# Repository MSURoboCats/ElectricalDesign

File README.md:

# Robocats Club PCB Files Repository

## Overview
Welcome to the Robocats Club PCB Files Repository! This repository contains all the necessary PCB design files, schematics, and related documentation for our club's various electronics projects. Our aim is to create, share, and improve PCB designs that can be used in robotics, automation, and other related fields.

## Getting Started
To use these files, clone the repository to your local machine:

```bash
git clone https://github.com/MSURoboCats/PcbDesign.git
```

You will need KiCad 7.0 to open and edit the `.kicad_pcb` and schematic files.

## Contribution Guidelines
We welcome contributions from all club members and the broader community. To contribute:

1. **Fork the Repository**: Create your own fork of the project.
2. **Create a Feature Branch**: Make your changes in a new branch.
3. **Commit Your Changes**: Commit your changes with clear and detailed commit messages.
4. **Submit a Pull Request**: Create a pull request for your changes to be reviewed.

Please ensure your designs meet our design standards and include necessary documentation and comments.

## Project Status
- [NewSub2023]: In-progress
- [OldSub2022]: Completed

## License
This project is licensed under the [MIT License](LICENSE) - see the LICENSE file for details.

## Contact
- Lead Designer: Peter Buckley
- Email: peterbuckley3636@gmail.com

For more information or to get involved, please join our discord.

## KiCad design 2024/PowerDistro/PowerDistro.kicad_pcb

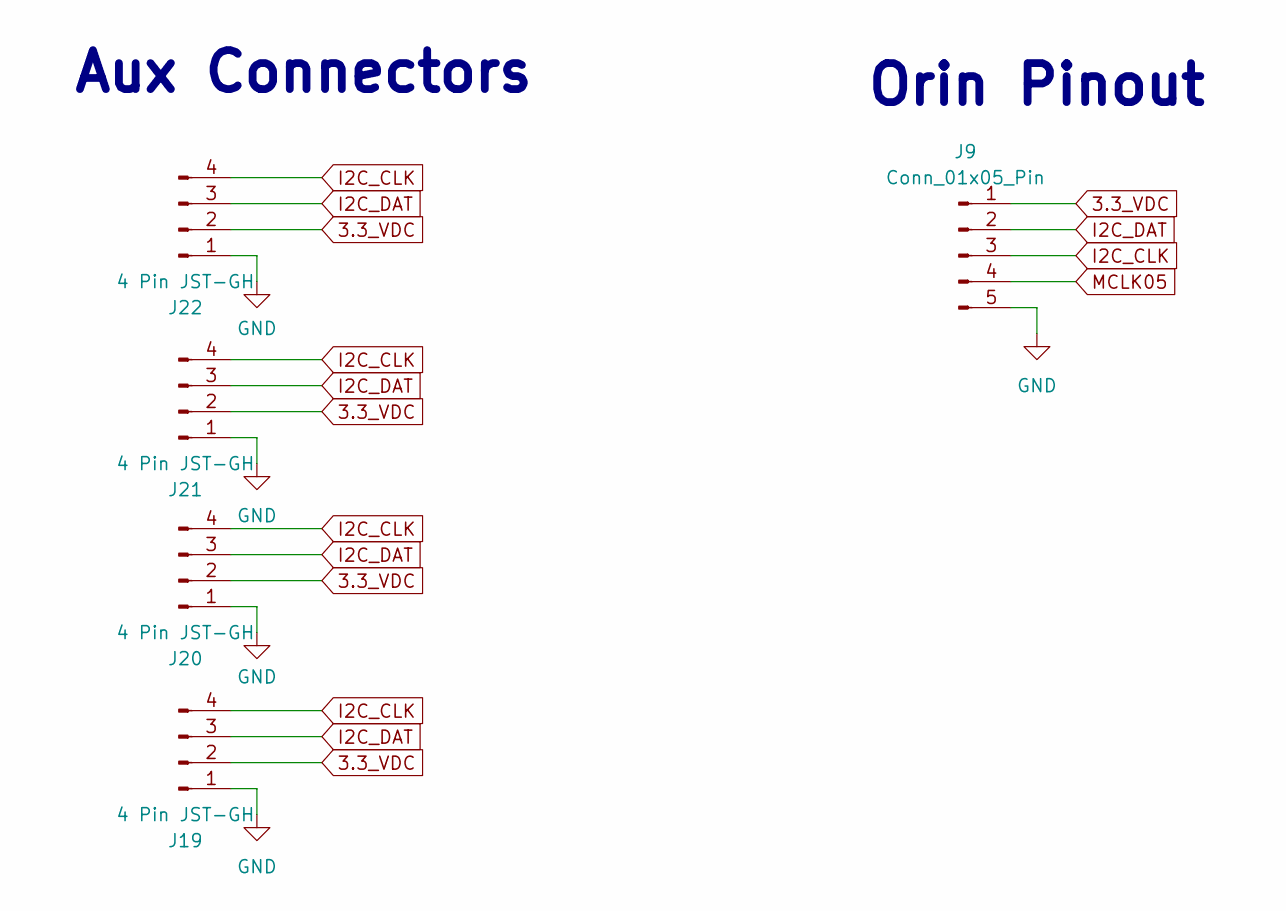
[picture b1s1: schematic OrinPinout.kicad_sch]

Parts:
J9: Conn_01x05_Pin; PinHeader_1x05_P2.54mm_Vertical
J19, J20, J21, J22: 4 Pin JST-GH; JST_XH_B4B-XH-A_1x04_P2.50mm_Vertical

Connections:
3.3_VDC: J9.1, J19.2, J20.2, J21.2, J22.2; also elsewhere on the board
GND: J9.5, J19.1, J20.1, J21.1, J22.1; also elsewhere on the board
I2C_CLK: J9.3, J19.4, J20.4, J21.4, J22.4; also elsewhere on the board
I2C_DAT: J9.2, J19.3, J20.3, J21.3, J22.3; also elsewhere on the board
MCLK05: J9.4

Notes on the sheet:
Orin Pinout
Aux Connectors

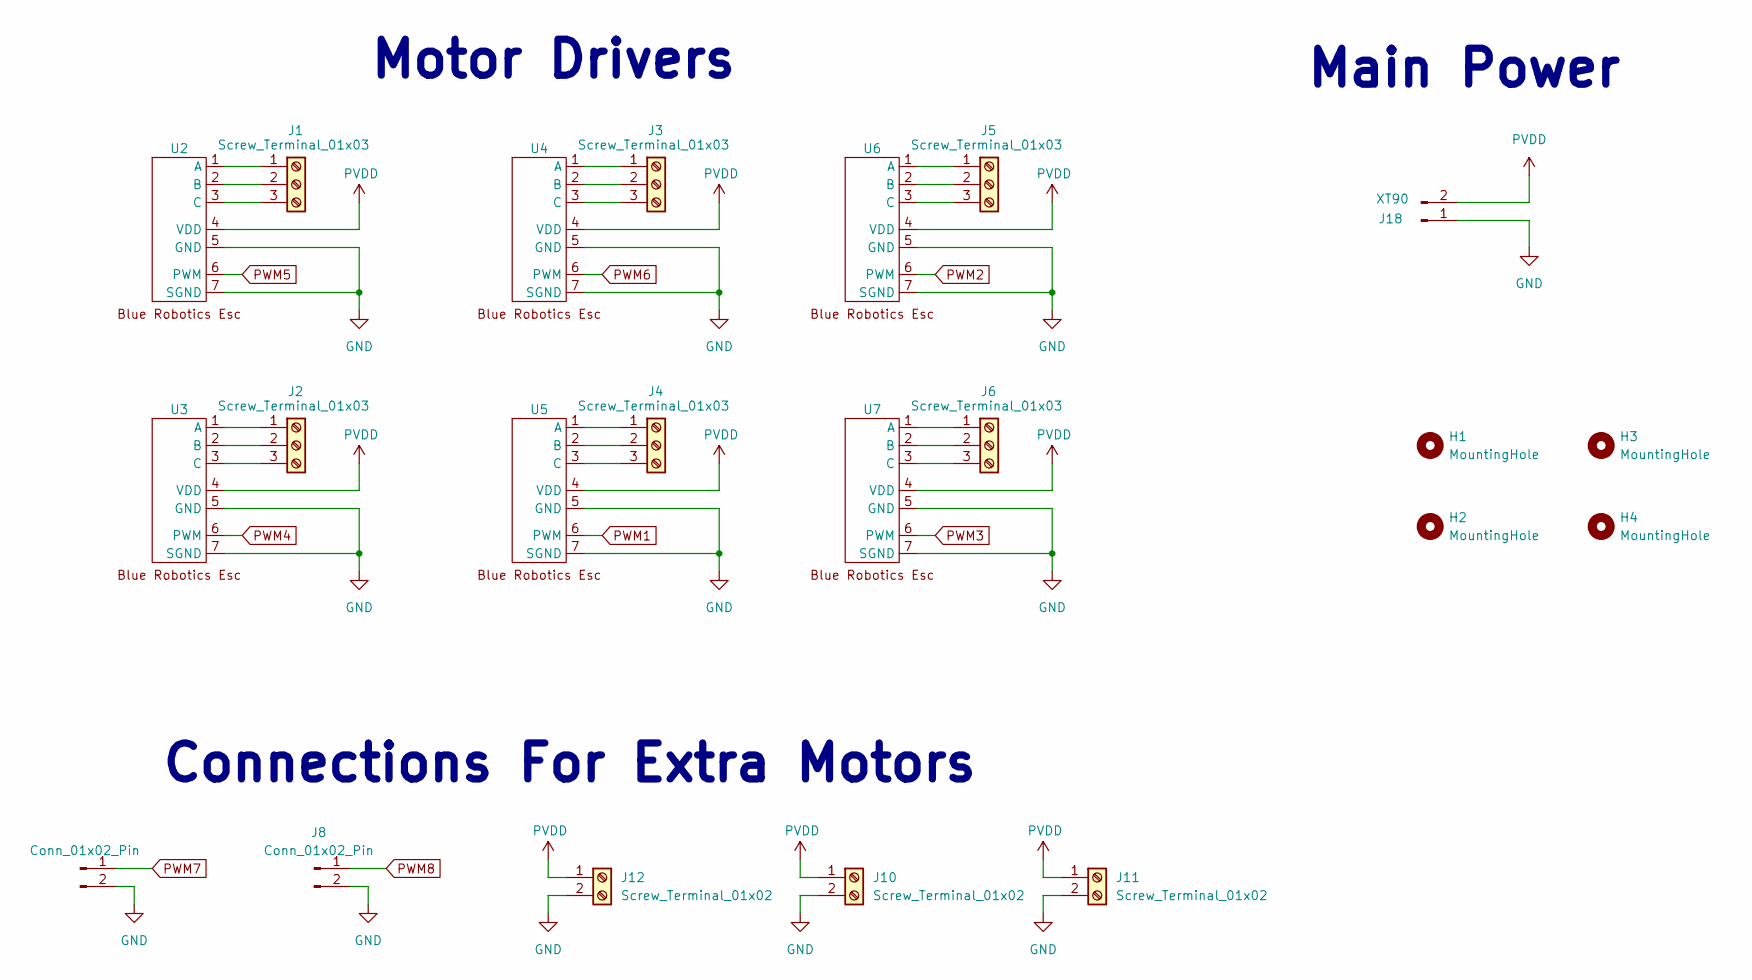
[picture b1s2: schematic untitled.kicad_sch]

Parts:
H1, H2, H3, H4: MountingHole; MountingHole_5.3mm_M5
J1, J2, J3, J4, J5, J6: Screw_Terminal_01x03; 691311500103
J7, J8: Conn_01x02_Pin; PinHeader_1x02_P2.54mm_Vertical
J10, J11, J12: Screw_Terminal_01x02; 691321100002
J18: XT90; XT90PB
U2, U3, U4, U5, U6, U7: BlueRoboticsESC

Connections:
GND: J7.2, J8.2, J10.2, J11.2, J12.2, J18.1, U2.5 (GND), U2.7 (SGND), U3.5 (GND), U3.7 (SGND), U4.5 (GND), U4.7 (SGND), U5.5 (GND), U5.7 (SGND), U6.5 (GND), U6.7 (SGND), U7.5 (GND), U7.7 (SGND); also elsewhere on the board
unnamed: J1.1, U2.1 (A)
unnamed: J1.2, U2.2 (B)
unnamed: J1.3, U2.3 (C)
unnamed: J2.1, U3.1 (A)
unnamed: J2.2, U3.2 (B)
unnamed: J2.3, U3.3 (C)
unnamed: J3.1, U4.1 (A)
unnamed: J3.2, U4.2 (B)
unnamed: J3.3, U4.3 (C)
unnamed: J4.1, U5.1 (A)
unnamed: J4.2, U5.2 (B)
unnamed: J4.3, U5.3 (C)
unnamed: J5.1, U6.1 (A)
unnamed: J5.2, U6.2 (B)
unnamed: J5.3, U6.3 (C)
unnamed: J6.1, U7.1 (A)
unnamed: J6.2, U7.2 (B)
unnamed: J6.3, U7.3 (C)
PVDD: J10.1, J11.1, J12.1, J18.2, U2.4 (VDD), U3.4 (VDD), U4.4 (VDD), U5.4 (VDD), U6.4 (VDD), U7.4 (VDD); also elsewhere on the board
PWM1: U5.6 (PWM); also elsewhere on the board
PWM2: U6.6 (PWM); also elsewhere on the board
PWM3: U7.6 (PWM); also elsewhere on the board
PWM4: U3.6 (PWM); also elsewhere on the board
PWM5: U2.6 (PWM); also elsewhere on the board
PWM6: U4.6 (PWM); also elsewhere on the board
PWM7: J7.1; also elsewhere on the board
PWM8: J8.1; also elsewhere on the board

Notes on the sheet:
Motor Drivers
Main Power
Connections For Extra Motors

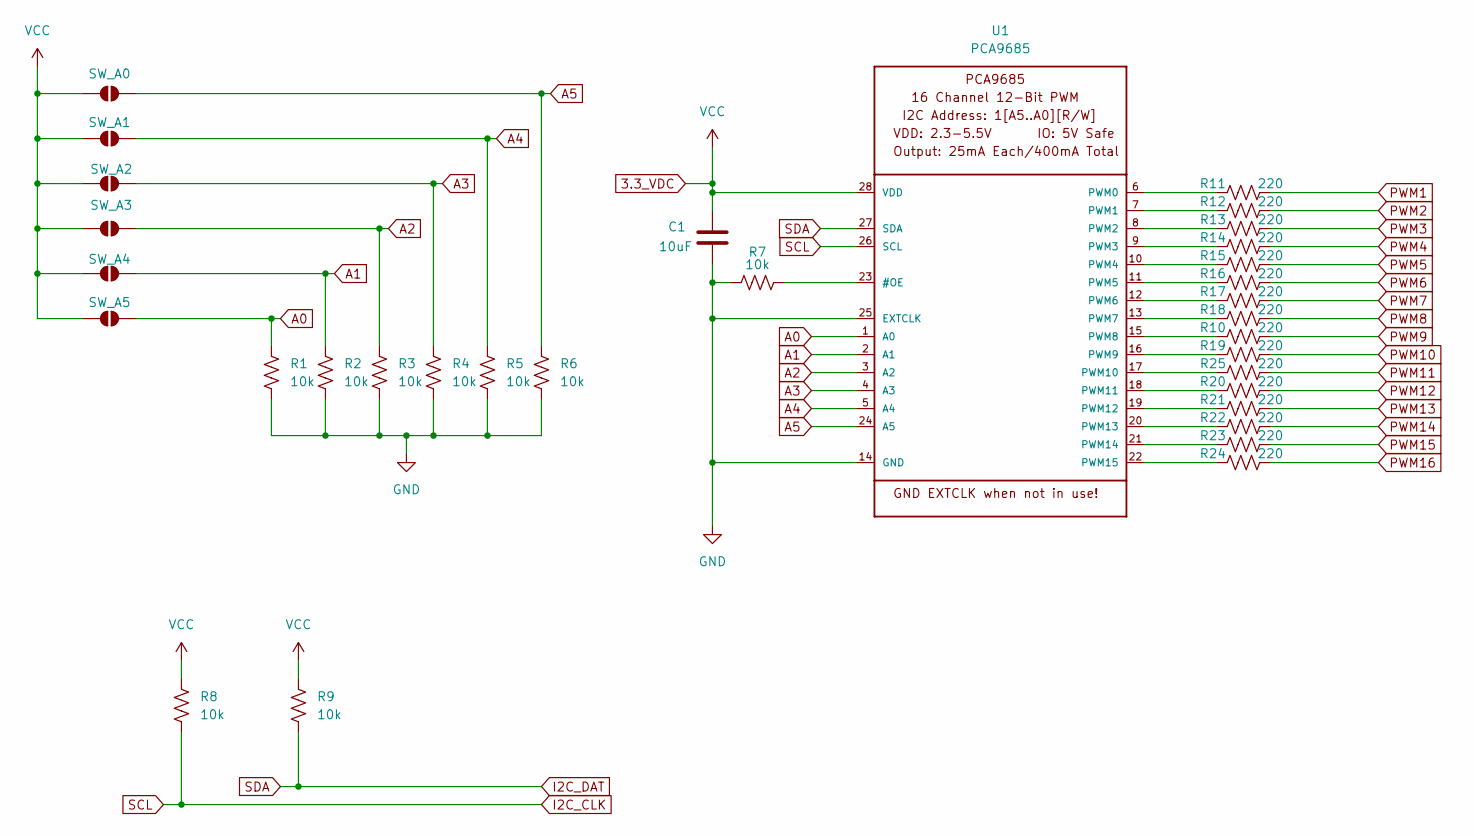
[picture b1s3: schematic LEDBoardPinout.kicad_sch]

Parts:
C1: 10uF; C_1206_3216Metric
R1, R2, R3, R4, R5, R6, R7, R8, R9: 10k; R_0603_1608Metric
R10, R11, R12, R13, R14, R15, R16, R17, R18, R19, R20, R21, R22, R23, R24, R25: 220; R_0603_1608Metric
SW_A0, SW_A1, SW_A2, SW_A3, SW_A4, SW_A5: SolderJumper_2_Open; SolderJumper-2_P1.3mm_Open_RoundedPad1.0x1.5mm
U1: PCA9685; TSSOP28

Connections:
3.3_VDC: C1.1, R8.1, R9.1, SW_A0.1 (A), SW_A1.1 (A), SW_A2.1 (A), SW_A3.1 (A), SW_A4.1 (A), SW_A5.1 (A), U1.28 (VDD); also elsewhere on the board
A0: R1.1, SW_A5.2 (B), U1.1 (A0)
A1: R2.1, SW_A4.2 (B), U1.2 (A1)
A2: R3.1, SW_A3.2 (B), U1.3 (A2)
A3: R4.1, SW_A2.2 (B), U1.4 (A3)
A4: R5.1, SW_A1.2 (B), U1.5 (A4)
A5: R6.1, SW_A0.2 (B), U1.24 (A5)
GND: C1.2, R1.2, R2.2, R3.2, R4.2, R5.2, R6.2, R7.2, U1.14 (GND), U1.25 (EXTCLK); also elsewhere on the board
I2C_CLK: R8.2, U1.26 (SCL); also elsewhere on the board
I2C_DAT: R9.2, U1.27 (SDA); also elsewhere on the board
unnamed: R7.1, U1.23 (#OE)
unnamed: R11.1, U1.6 (PWM0)
unnamed: R12.1, U1.7 (PWM1)
unnamed: R13.1, U1.8 (PWM2)
unnamed: R14.1, U1.9 (PWM3)
unnamed: R15.1, U1.10 (PWM4)
unnamed: R16.1, U1.11 (PWM5)
unnamed: R17.1, U1.12 (PWM6)
unnamed: R18.1, U1.13 (PWM7)
unnamed: R10.1, U1.15 (PWM8)
unnamed: R19.1, U1.16 (PWM9)
unnamed: R25.1, U1.17 (PWM10)
unnamed: R20.1, U1.18 (PWM11)
unnamed: R21.1, U1.19 (PWM12)
unnamed: R22.1, U1.20 (PWM13)
unnamed: R23.1, U1.21 (PWM14)
unnamed: R24.1, U1.22 (PWM15)
PWM1: R11.2; also elsewhere on the board
PWM2: R12.2; also elsewhere on the board
PWM3: R13.2; also elsewhere on the board
PWM4: R14.2; also elsewhere on the board
PWM5: R15.2; also elsewhere on the board
PWM6: R16.2; also elsewhere on the board
PWM7: R17.2; also elsewhere on the board
PWM8: R18.2; also elsewhere on the board
PWM9: R10.2; also elsewhere on the board
PWM10: R19.2; also elsewhere on the board
PWM11: R25.2; also elsewhere on the board
PWM12: R20.2; also elsewhere on the board
PWM13: R21.2; also elsewhere on the board
PWM14: R22.2; also elsewhere on the board
PWM15: R23.2; also elsewhere on the board
PWM16: R24.2; also elsewhere on the board

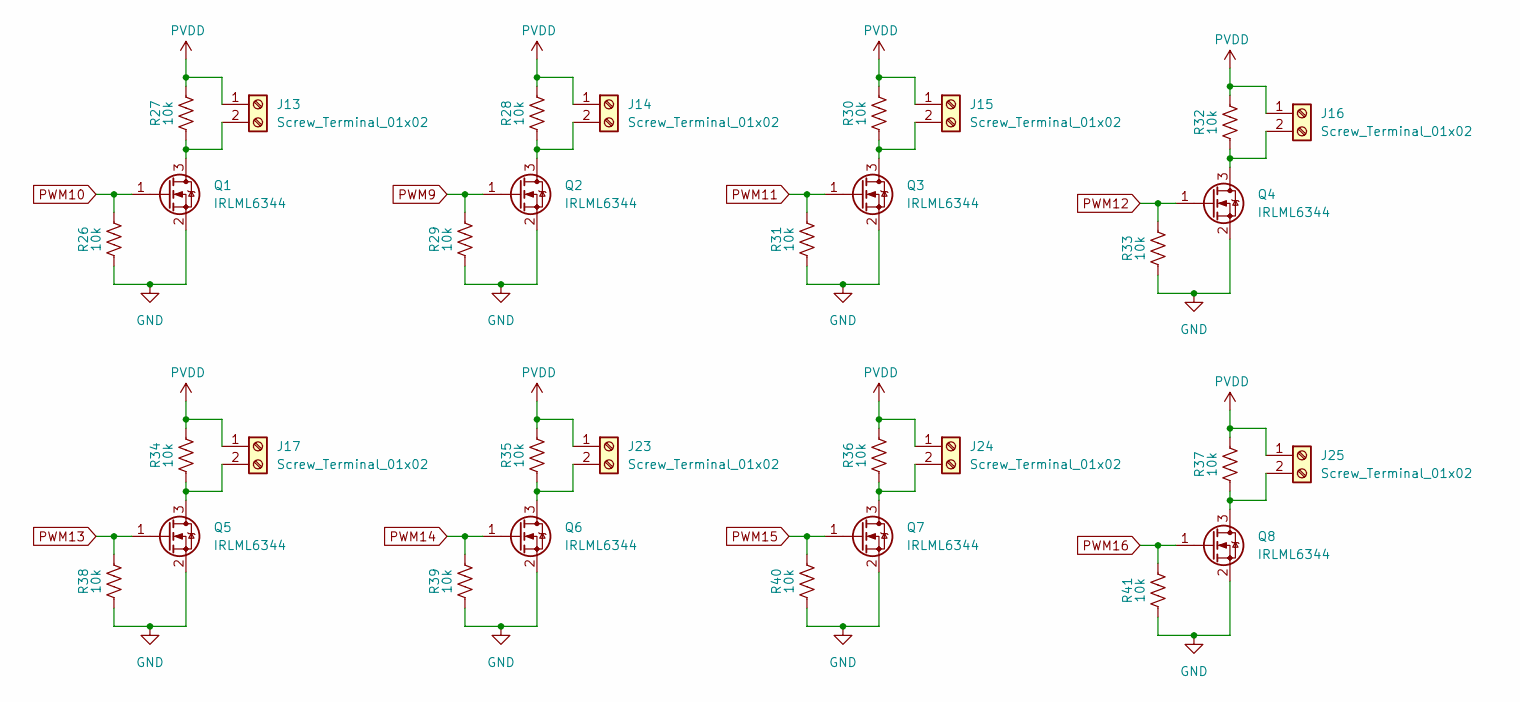
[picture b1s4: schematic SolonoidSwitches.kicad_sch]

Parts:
J13, J14, J15, J16, J17, J23, J24, J25: Screw_Terminal_01x02; 691321100002
Q1, Q2, Q3, Q4, Q5, Q6, Q7, Q8: IRLML6344; SOT-23
R26, R27, R28, R29, R30, R31, R32, R33, R34, R35, R36, R37, R38, R39, R40, R41: 10k; R_0603_1608Metric

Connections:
GND: Q1.2 (S), Q2.2 (S), Q3.2 (S), Q4.2 (S), Q5.2 (S), Q6.2 (S), Q7.2 (S), Q8.2 (S), R26.2, R29.2, R31.2, R33.2, R38.2, R39.2, R40.2, R41.2; also elsewhere on the board
unnamed: J13.2, Q1.3 (D), R27.2
unnamed: J14.2, Q2.3 (D), R28.2
unnamed: J15.2, Q3.3 (D), R30.2
unnamed: J16.2, Q4.3 (D), R32.2
unnamed: J17.2, Q5.3 (D), R34.2
unnamed: J23.2, Q6.3 (D), R35.2
unnamed: J24.2, Q7.3 (D), R36.2
unnamed: J25.2, Q8.3 (D), R37.2
PVDD: J13.1, J14.1, J15.1, J16.1, J17.1, J23.1, J24.1, J25.1, R27.1, R28.1, R30.1, R32.1, R34.1, R35.1, R36.1, R37.1; also elsewhere on the board
PWM9: Q2.1 (G), R29.1; also elsewhere on the board
PWM10: Q1.1 (G), R26.1; also elsewhere on the board
PWM11: Q3.1 (G), R31.1; also elsewhere on the board
PWM12: Q4.1 (G), R33.1; also elsewhere on the board
PWM13: Q5.1 (G), R38.1; also elsewhere on the board
PWM14: Q6.1 (G), R39.1; also elsewhere on the board
PWM15: Q7.1 (G), R40.1; also elsewhere on the board
PWM16: Q8.1 (G), R41.1; also elsewhere on the board

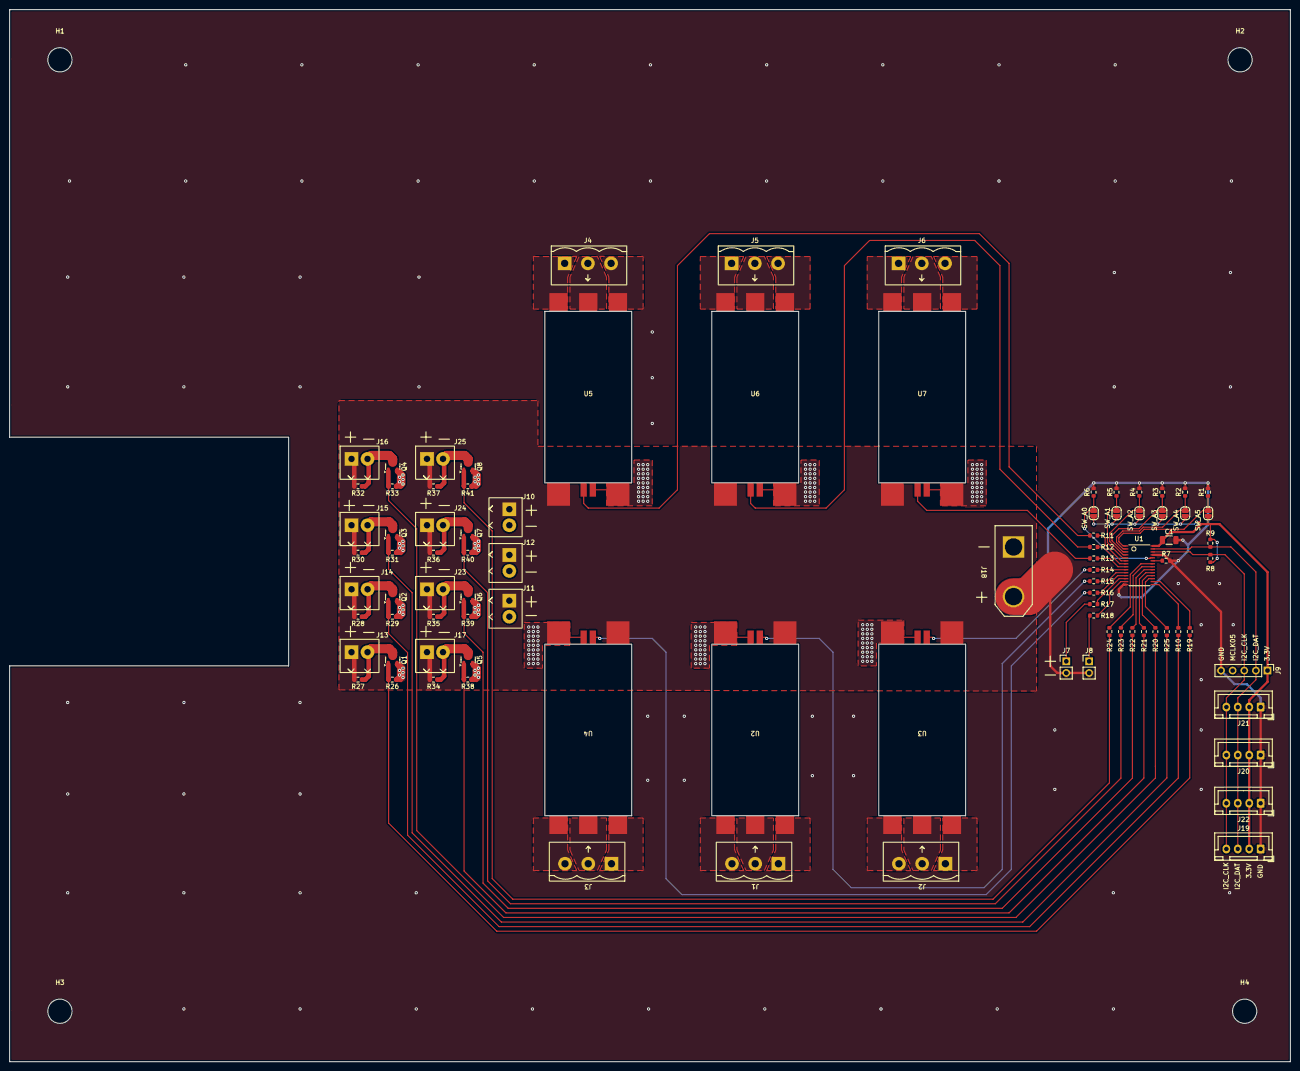
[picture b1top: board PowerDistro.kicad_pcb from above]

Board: 2 copper layers, 280.0 x 230.0 mm, 92 parts (0 on the bottom side), 70 nets.

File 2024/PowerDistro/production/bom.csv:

Designator,Footprint,Quantity,Value,LCSC Part #,
C1,1206,1,10uF,,
"J1, J2, J3, J4, J5, J6",Screw Terminal,6,Screw_Terminal_01x03,,have 3
"J10, J11, J12, J13, J14, J15, J16, J17, J23, J24, J25",Screw Terminal,11,Screw_Terminal_01x02,,
J18,XT90PB,1,XT90,,have
"J19, J20, J21, J22",JST_XH_B4B-XH-A_1x04_P2.50mm_Vertical,4,4 Pin JST-GH,,
"J7, J8",PinHeader_1x02_P2.54mm_Vertical,2,Conn_01x02_Pin,,have
J9,PinHeader_1x05_P2.54mm_Vertical,1,Conn_01x05_Pin,,
"Q1, Q2, Q3, Q4, Q5, Q6, Q7, Q8",SOT-23,8,IRLML6344,,
"R1, R2, R26, R27, R28, R29, R3, R30, R31, R32, R33, R34, R35, R36, R37, R38, R39, R4, R40, R41, R5, R6, R7, R8, R9",603,25,10k,,
"R10, R11, R12, R13, R14, R15, R16, R17, R18, R19, R20, R21, R22, R23, R24, R25",603,16,220,,
U1,TSSOP28,1,PCA9685,,
"U2, U3, U4, U5, U6, U7",BlueRoboticsESC,6,~,,have 1 unsused and 6 in current board

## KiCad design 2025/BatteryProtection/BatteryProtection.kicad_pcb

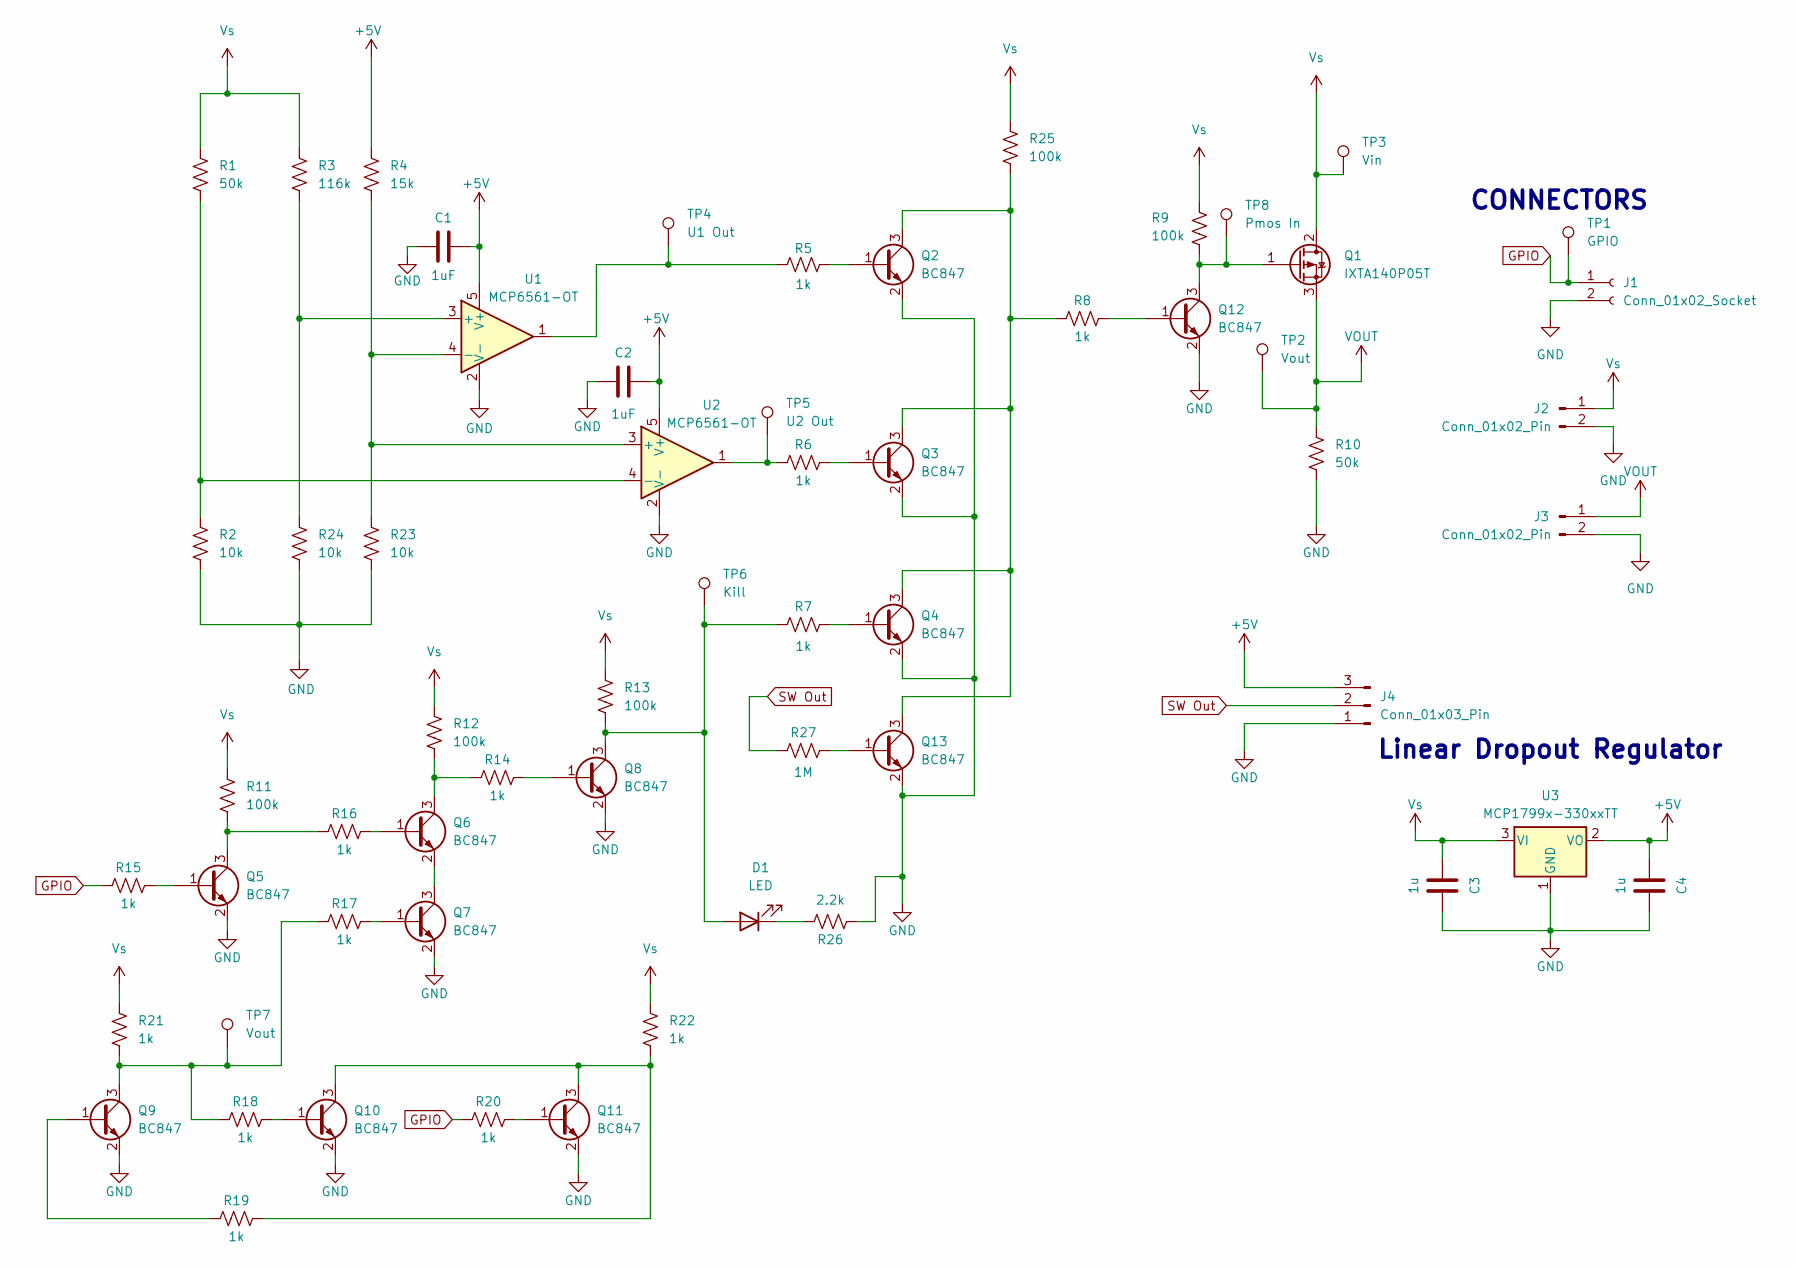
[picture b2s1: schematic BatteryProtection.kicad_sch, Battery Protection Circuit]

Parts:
C1, C2: 1uF; C_0603_1608Metric_Pad1.08x0.95mm_HandSolder
C3, C4: 1u; C_0603_1608Metric_Pad1.08x0.95mm_HandSolder
D1: LED; LED_0805_2012Metric
J1: Conn_01x02_Socket; JST_XH_B2B-XH-A_1x02_P2.50mm_Vertical
J2: Conn_01x02_Pin; XT90PW-M
J3: Conn_01x02_Pin; XT90PW-F
J4: Conn_01x03_Pin; JST_B3B-XH-A
Q1: IXTA140P05T; TO-263-2
Q2, Q3, Q4, Q5, Q6, Q7, Q8, Q9, Q10, Q11, Q12, Q13: BC847; SOT-23
R1, R10: 50k; R_0603_1608Metric_Pad0.98x0.95mm_HandSolder
R2, R23, R24: 10k; R_0603_1608Metric_Pad0.98x0.95mm_HandSolder
R3: 116k; R_0603_1608Metric_Pad0.98x0.95mm_HandSolder
R4: 15k; R_0603_1608Metric_Pad0.98x0.95mm_HandSolder
R5, R6, R7, R8, R14, R15, R16, R17, R18, R19, R20, R21, R22: 1k; R_0603_1608Metric_Pad0.98x0.95mm_HandSolder
R9, R11, R12, R13, R25: 100k; R_0603_1608Metric_Pad0.98x0.95mm_HandSolder
R26: 2.2k; R_0603_1608Metric_Pad0.98x0.95mm_HandSolder
R27: 1M; R_0603_1608Metric_Pad0.98x0.95mm_HandSolder
TP1: GPIO; TestPoint_Pad_D1.5mm
TP2, TP7: Vout; TestPoint_Pad_D1.5mm
TP3: Vin; TestPoint_Pad_D1.5mm
TP4: U1 Out; TestPoint_Pad_D1.5mm
TP5: U2 Out; TestPoint_Pad_D1.5mm
TP6: Kill; TestPoint_Pad_D1.5mm
TP8: Pmos In; TestPoint_Pad_D1.5mm
U1, U2: MCP6561-OT; SOT-23-5
U3: MCP1799x-330xxTT; SOT-23

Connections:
+5V: C1.2, C2.2, C4.1, J4.3, R4.1, U1.5 (V+), U2.5 (V+), U3.2 (VO)
GND: C1.1, C2.1, C3.2, C4.2, J1.2, J2.2, J3.2, J4.1, Q2.2 (E), Q3.2 (E), Q4.2 (E), Q5.2 (E), Q7.2 (E), Q8.2 (E), Q9.2 (E), Q10.2 (E), Q11.2 (E), Q12.2 (E), Q13.2 (E), R2.2, R10.1, R23.2, R24.2, R26.1, U1.2 (V-), U2.2 (V-), U3.1 (GND)
GPIO: J1.1, R15.1, R20.1, TP1.1
unnamed: D1.2 (A), Q8.3 (C), R7.1, R13.1, TP6.1
unnamed: D1.1 (K), R26.2
unnamed: Q1.1 (G), Q12.3 (C), R9.1, TP8.1
unnamed: Q2.1 (B), R5.1
unnamed: Q3.1 (B), R6.2
unnamed: Q4.1 (B), R7.2
unnamed: Q5.1 (B), R15.2
unnamed: Q5.3 (C), R11.1, R16.1
unnamed: Q6.1 (B), R16.2
unnamed: Q6.3 (C), R12.1, R14.1
unnamed: Q6.2 (E), Q7.3 (C)
unnamed: Q7.1 (B), R17.2
unnamed: Q8.1 (B), R14.2
unnamed: Q9.1 (B), R19.1
unnamed: Q9.3 (C), R17.1, R18.1, R21.2, TP7.1
unnamed: Q10.1 (B), R18.2
unnamed: Q10.3 (C), Q11.3 (C), R19.2, R22.2
unnamed: Q11.1 (B), R20.2
unnamed: Q12.1 (B), R8.1
unnamed: Q13.1 (B), R27.2
unnamed: Q2.3 (C), Q3.3 (C), Q4.3 (C), Q13.3 (C), R8.2, R25.1
unnamed: R5.2, TP4.1, U1.1
unnamed: R6.1, TP5.1, U2.1
unnamed: R3.2, R24.1, U1.3 (+)
unnamed: R4.2, R23.1, U1.4 (-), U2.3 (+)
unnamed: R1.2, R2.1, U2.4 (-)
SW Out: J4.2, R27.1
VOUT: J3.1, Q1.3 (S), R10.2, TP2.1
Vs: C3.1, J2.1, Q1.2 (D), R1.1, R3.1, R9.2, R11.2, R12.2, R13.2, R21.1, R22.1, R25.2, TP3.1, U3.3 (VI)

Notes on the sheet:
Linear Dropout Regulator
CONNECTORS

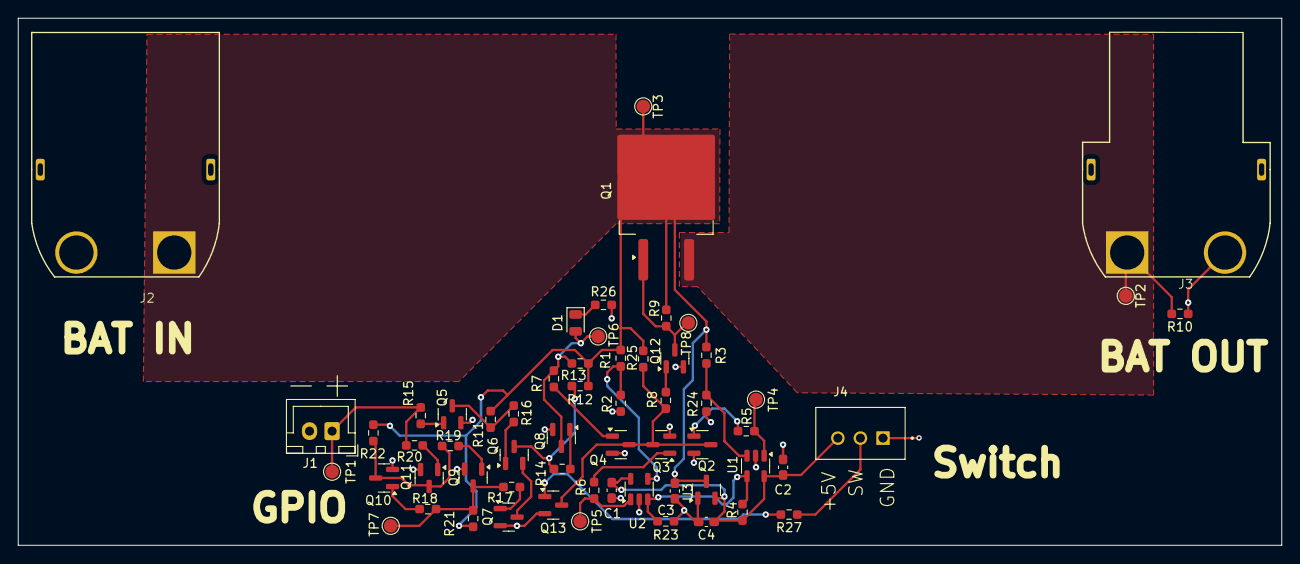
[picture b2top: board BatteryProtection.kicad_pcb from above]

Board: 2 copper layers, 140.1 x 58.4 mm, 60 parts (0 on the bottom side), 32 nets.

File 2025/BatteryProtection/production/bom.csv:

Designator,Footprint,Quantity,Value,LCSC Part #
"C1, C2",0603,2,1uF,
"C3, C4",0603,2,1u,
D1,0805,1,LED,
J1,JST_XH_B2B-XH-A_1x02_P2.50mm_Vertical,1,Conn_01x02_Socket,
J2,XT90PW-M,1,Conn_01x02_Pin,
J3,XT90PW-F,1,Conn_01x02_Pin,
Q1,TO-263-2,1,IXTA140P05T,
"Q10, Q11, Q12, Q2, Q3, Q4, Q5, Q6, Q7, Q8, Q9",SOT-23,11,BC847,
"R1, R10",0603,2,50k,
"R11, R12, R13, R25, R9",0603,5,100k,
"R14, R15, R16, R17, R18, R19, R20, R21, R22, R5, R6, R7, R8",0603,13,1k,
"R2, R23, R24",0603,3,10k,
R26,0603,1,2.2k,
R3,0603,1,116k,
R4,0603,1,15k,
TP1,TestPoint_Pad_D1.5mm,1,GPIO,
"TP2, TP7",TestPoint_Pad_D1.5mm,2,Vout,
TP3,TestPoint_Pad_D1.5mm,1,Vin,
TP4,TestPoint_Pad_D1.5mm,1,U1 Out,
TP5,TestPoint_Pad_D1.5mm,1,U2 Out,
TP6,TestPoint_Pad_D1.5mm,1,Kill,
TP8,TestPoint_Pad_D1.5mm,1,Pmos In,
"U1, U2",SOT-23-5,2,MCP6561-OT,
U3,SOT-23,1,MCP1799x-330xxTT,

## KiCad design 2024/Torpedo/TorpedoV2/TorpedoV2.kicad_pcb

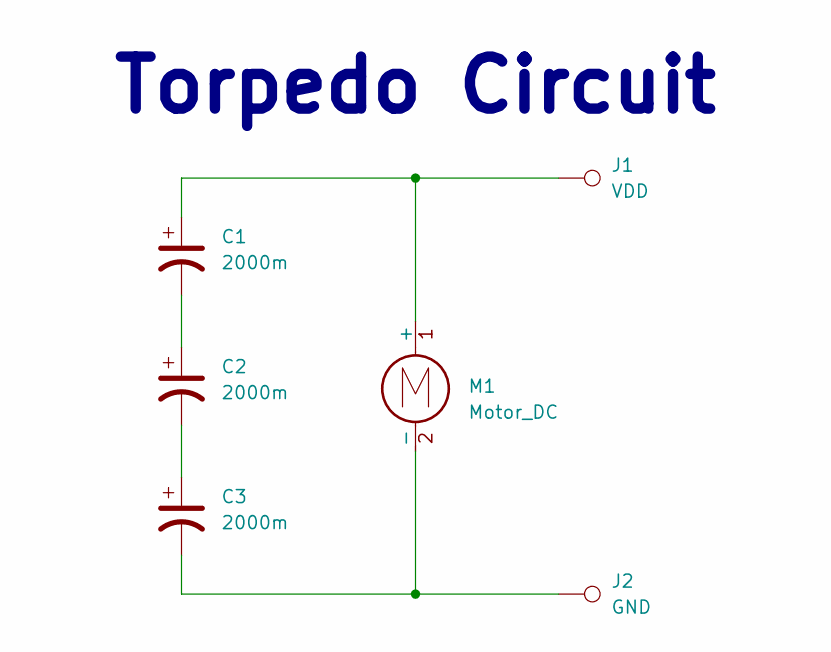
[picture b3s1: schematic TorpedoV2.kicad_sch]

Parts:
C1, C2, C3: 2000m; CP_Radial_D8.0mm_P3.50mm
J1: VDD; MillMax4650
J2: GND; MillMax4650
M1: Motor_DC; PPN13

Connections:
unnamed: C1.2, C2.1
unnamed: C2.2, C3.1
unnamed: C1.1, J1.1, M1.1 (+)
unnamed: C3.2, J2.1, M1.2 (-)

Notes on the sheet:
Torpedo Circuit

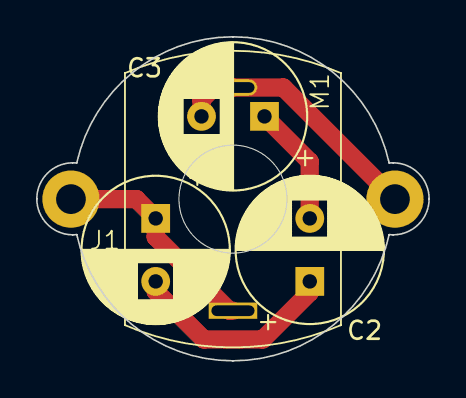
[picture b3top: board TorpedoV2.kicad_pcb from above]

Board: 2 copper layers, 21.8 x 18.0 mm, 6 parts (0 on the bottom side), 4 nets.

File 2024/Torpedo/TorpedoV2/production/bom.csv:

Designator,Footprint,Quantity,Value,LCSC Part #
"C1, C2, C3",CP_Radial_D8.0mm_P3.50mm,3,2000m,
J1,MillMax4650,1,VDD,
J2,MillMax4650,1,GND,
M1,PPN13,1,Motor_DC,

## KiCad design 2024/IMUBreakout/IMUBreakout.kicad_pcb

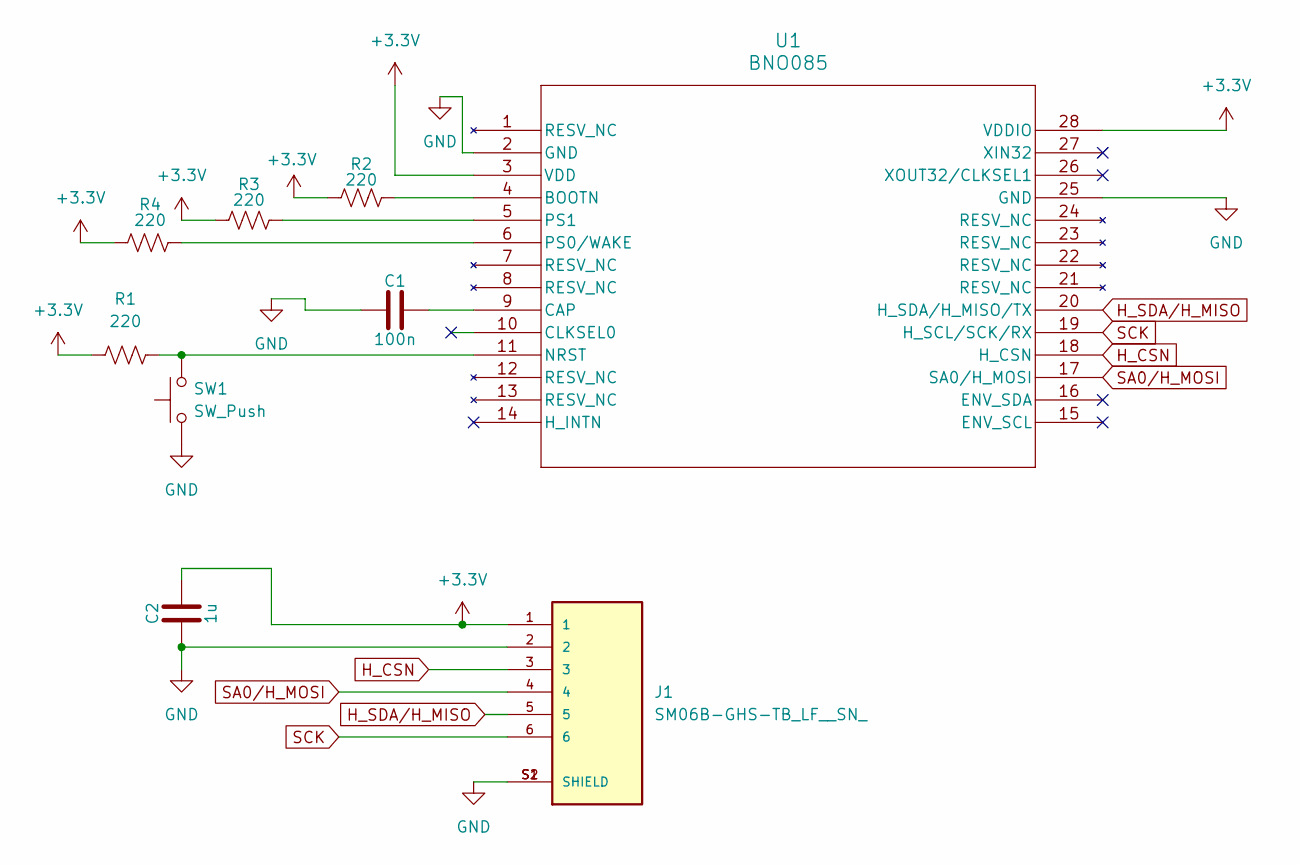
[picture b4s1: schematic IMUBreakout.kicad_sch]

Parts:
C1: 100n; C_0603_1608Metric
C2: 1u; C_0603_1608Metric
J1: SM06B-GHS-TB_LF__SN_; JST_SM06B-GHS-TB_LF__SN_; PARTREV N/A
R1, R2, R3, R4: 220; R_0603_1608Metric
SW1: SW_Push; SW_Push_1P1T_NO_6x6mm_H9.5mm
U1: BNO085; LGA-28_CEV

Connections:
SA0/H_MOSI: J1.4, U1.17 (SA0/H_MOSI)
+3.3V: C2.2, J1.1, R1.1, R2.1, R3.1, R4.1, U1.3 (VDD), U1.28 (VDDIO)
GND: C1.1, C2.1, J1.2, J1.S1 (SHIELD), J1.S2 (SHIELD), SW1.1, U1.2 (GND), U1.25 (GND)
H_CSN: J1.3, U1.18 (H_CSN)
H_SDA/H_MISO: J1.5, U1.20 (H_SDA/H_MISO/TX)
unnamed: R2.2, U1.4 (BOOTN)
unnamed: C1.2, U1.9 (CAP)
unnamed: R1.2, SW1.2, U1.11 (NRST)
unnamed: R4.2, U1.6 (PS0/WAKE)
unnamed: R3.2, U1.5 (PS1)
SCK: J1.6, U1.19 (H_SCL/SCK/RX)

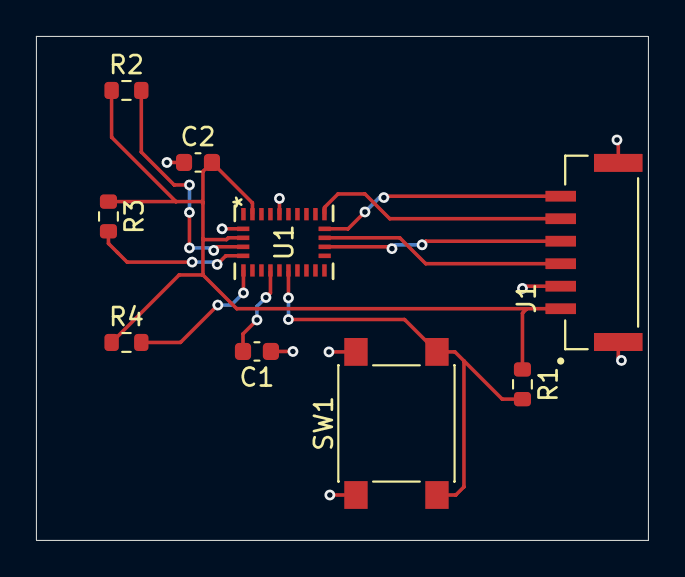
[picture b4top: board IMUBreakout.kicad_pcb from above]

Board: 2 copper layers, 34.0 x 28.0 mm, 9 parts (0 on the bottom side), 11 nets.

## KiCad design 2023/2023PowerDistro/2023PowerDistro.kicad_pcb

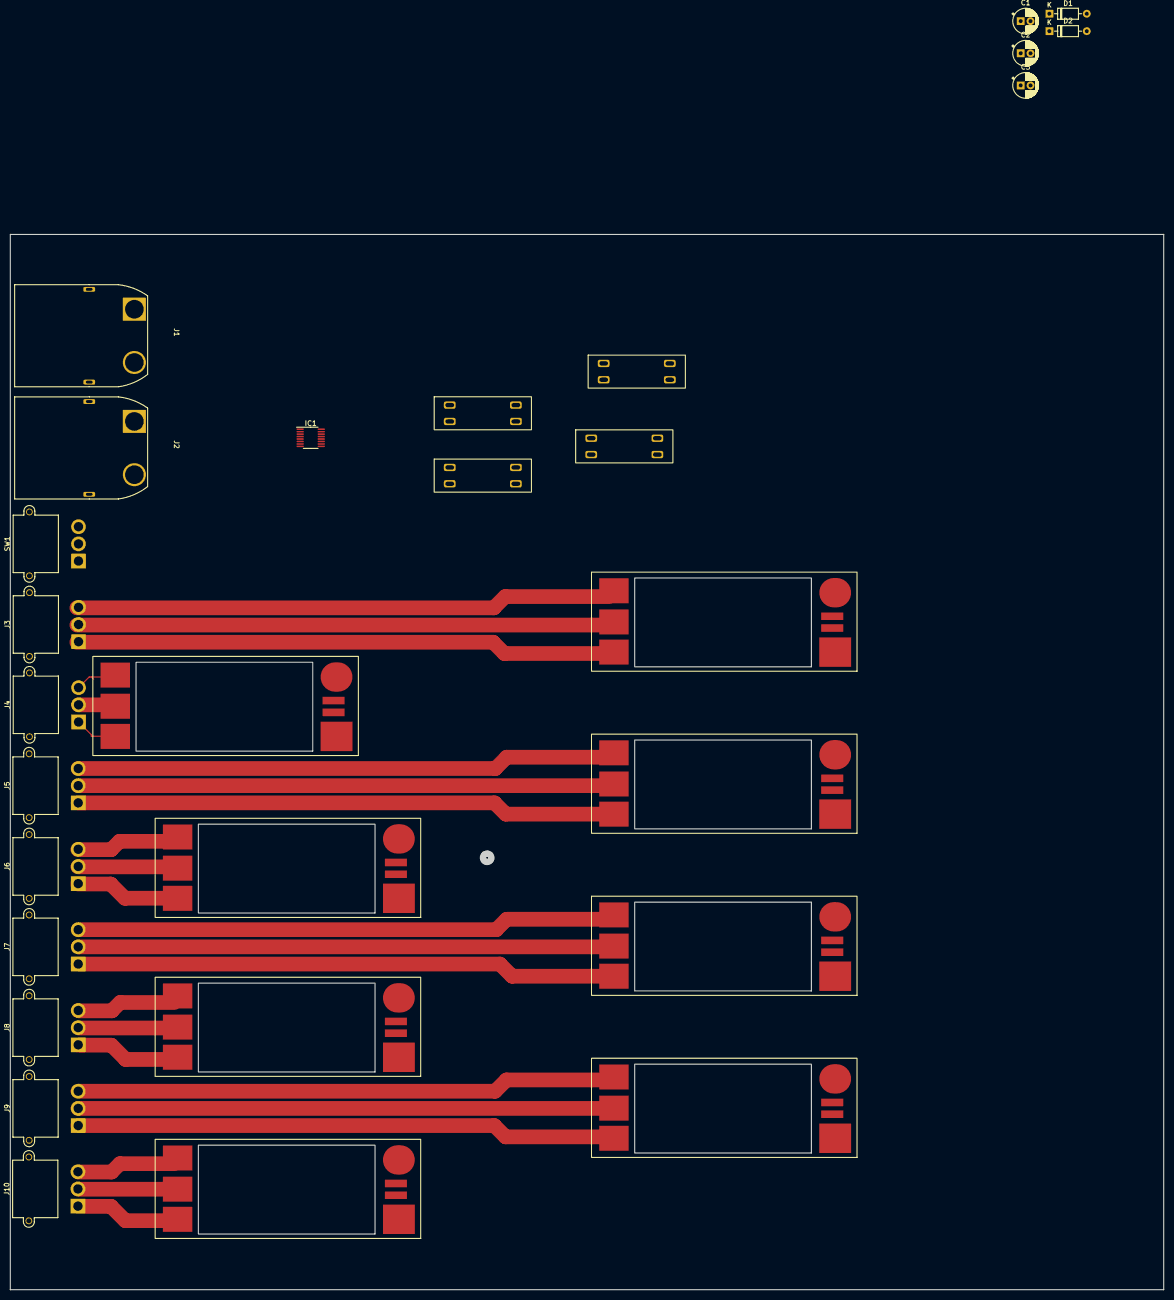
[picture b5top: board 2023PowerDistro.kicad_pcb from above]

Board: 2 copper layers, 235.0 x 215.0 mm, 29 parts (0 on the bottom side), 32 nets.

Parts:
C1, C2: 1uF; CP_Radial_D5.0mm_P2.00mm
C3: 0.33uF; CP_Radial_D5.0mm_P2.00mm
D1, D2: BAT41; D_DO-35_SOD27_P7.62mm_Horizontal
F1, F2, F3, F4: 30A; 3557-15
IC1: MSOP-16_3x4mm_P0.5mm
J1: Battery 1 Input; XT90PW-M
J2: Battery 2 Input; XT90PW-M
J3, J4, J5, J6, J7, J8, J9, J10: MR30PW-M
SW1: Power Switch; MR30PW-M
Us1, Us2, Us4, Us5, Us6, Us7, Us8, Us9: BR-ESC

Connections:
GND: C1.2, C2.2, C3.2, IC1.15 (GND), J1.2 (-), J2.2 (-), SW1.1 (A), Us1.2 (-), Us1.4 (SG), Us2.2 (-), Us2.4 (SG), Us4.2 (-), Us4.4 (SG), Us5.2 (-), Us5.4 (SG), Us6.2 (-), Us6.4 (SG), Us7.2 (-), Us7.4 (SG), Us8.2 (-), Us8.4 (SG), Us9.2 (-), Us9.4 (SG)
unnamed: D1.2 (A), F1.1, F2.1, IC1.4 (Vin2)
unnamed: D1.1 (K), D2.1 (K), SW1.3 (C)
unnamed: D2.2 (A), F3.1, F4.1, IC1.13 (Vin1)
unnamed: IC1.1 (EN2), IC1.16 (EN1), SW1.2 (B)
unnamed: C1.1, IC1.14 (Vcc)
unnamed: F1.2, F2.2, J1.1 (+)
unnamed: F3.2, F4.2, J2.1 (+)
unnamed: J3.1 (A), Us2.5 (A)
unnamed: J3.2 (B), Us2.6 (B)
unnamed: J3.3 (C), Us2.7 (C)
unnamed: J4.1 (A), Us1.5 (A)
unnamed: J4.2 (B), Us1.6 (B)
unnamed: J4.3 (C), Us1.7 (C)
unnamed: J5.1 (A), Us4.5 (A)
unnamed: J5.2 (B), Us4.6 (B)
unnamed: J5.3 (C), Us4.7 (C)
unnamed: J6.1 (A), Us5.5 (A)
unnamed: J6.2 (B), Us5.6 (B)
unnamed: J6.3 (C), Us5.7 (C)
unnamed: J7.1 (A), Us6.5 (A)
unnamed: J7.2 (B), Us6.6 (B)
unnamed: J7.3 (C), Us6.7 (C)
unnamed: J8.1 (A), Us7.5 (A)
unnamed: J8.2 (B), Us7.6 (B)
unnamed: J8.3 (C), Us7.7 (C)
unnamed: J9.1 (A), Us8.5 (A)
unnamed: J9.2 (B), Us8.6 (B)
unnamed: J9.3 (C), Us8.7 (C)
unnamed: J10.1 (A), Us9.5 (A)
unnamed: J10.2 (B), J10.3 (C), Us9.7 (C)
VCC: C3.1, IC1.7 (OUT2), IC1.10 (OUT1), Us1.1 (+), Us2.1 (+), Us4.1 (+), Us5.1 (+), Us6.1 (+), Us7.1 (+), Us8.1 (+), Us9.1 (+)
